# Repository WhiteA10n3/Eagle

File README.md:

# 开源硬件项目

设计软件使用Eagle

现包含：
### Unicon系列开发板

#### Un_51
#### Un_Arduino
#### Un_ARM7
#### Un_AVR
#### Un_Battery
#### Un_Bus
#### Un_C8051F
#### Un_GPS
#### Un_Moto
#### Un_Net
#### Un_RF
#### Un_SecUSB
#### Un_TTL
#### Un_Usb
#### Un_Zigbee

多年前画的板子，会陆续开源出来
供大家学习使用
祝玩的愉快

@WhiteA10n3
2018.9.13

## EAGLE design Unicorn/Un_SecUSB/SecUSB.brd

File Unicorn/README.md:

# Unicon系列开发板

设计软件使用Eagle

#### Un_51
#### Un_Arduino
#### Un_ARM7
#### Un_AVR
#### Un_Battery
#### Un_Bus
#### Un_C8051F
#### Un_GPS
#### Un_Moto
#### Un_Net
#### Un_RF
#### Un_SecUSB
#### Un_TTL
#### Un_Usb
#### Un_Zigbee

@WhiteA10n3

2018.9.13

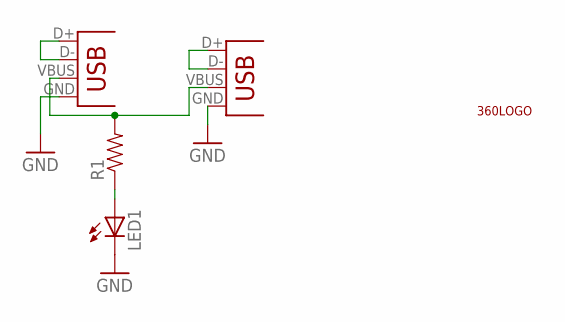
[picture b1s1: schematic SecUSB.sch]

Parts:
LED1: LED0603; LED-0603
R1: RESISTOR0603-RES; 0603-RES
U$1: 360LOGO_0.8
X2: USB_4-A-H_2; USB-A-H_2
X3: USB_4_3; USB-A-3

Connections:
GND: LED1.C, X2.GND, X3.GND
unnamed: R1.2, X2.VBUS, X3.VBUS
unnamed: X2.D+, X2.D-
unnamed: X3.D+, X3.D-
unnamed: LED1.A, R1.1

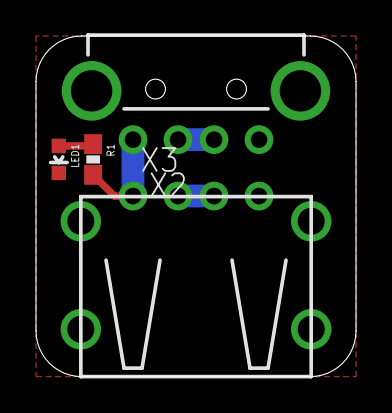
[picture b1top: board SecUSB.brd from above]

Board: 2 copper layers, 17.8 x 18.9 mm, 5 parts (1 on the bottom side), 5 nets.

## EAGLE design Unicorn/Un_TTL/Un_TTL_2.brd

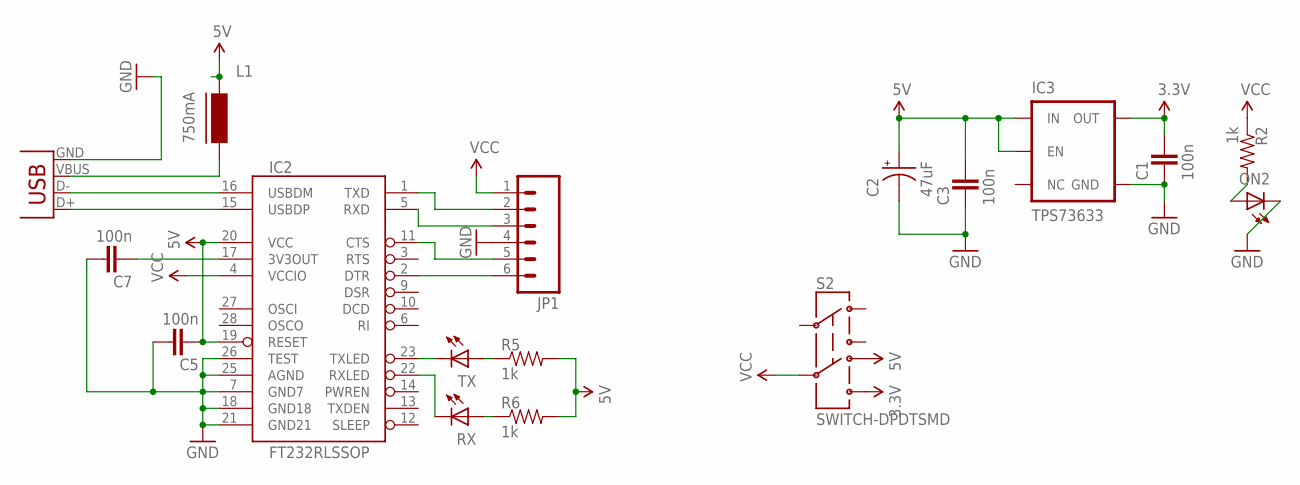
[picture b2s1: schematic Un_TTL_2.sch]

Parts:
C1, C3, C5, C7: 100n; 0603-CAP
C2: 47uF; EIA3216
IC2: FT232RLSSOP; SSOP28DB
IC3: TPS73633; SOT23-5
JP1: M06SIP; 1X06
L1: 750mA; FB805
ON2: LED0603; LED-0603
R2, R5, R6: 1k; 0603-RES
RX: LED0603; LED-0603
S2: SWITCH-DPDTSMD; AYZ0202
TX: LED0603; LED-0603
X2: USB_4-A-H; USB-A-H

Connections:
3.3V: C1.1, IC3.5 (OUT), S2.6
5V: C2.A (+), C3.1, C5.2, IC2.19 (RESET), IC2.20 (VCC), IC3.1 (IN), IC3.3 (EN), L1.1, R5.2, R6.2, S2.4
DTR: IC2.11 (CTS), JP1.5
GND: C1.2, C2.C (-), C3.2, C5.1, C7.1, IC2.7 (GND7), IC2.18 (GND18), IC2.21 (GND21), IC2.25 (AGND), IC2.26 (TEST), IC3.2 (GND), JP1.4, ON2.C, X2.GND
unnamed: L1.2, X2.VBUS
unnamed: ON2.A, R2.2
unnamed: R5.1, TX.A
unnamed: IC2.2 (DTR), JP1.6
unnamed: IC2.16 (USBDM), X2.D-
unnamed: IC2.15 (USBDP), X2.D+
unnamed: IC2.23 (TXLED), TX.C
unnamed: R6.1, RX.A
unnamed: IC2.22 (RXLED), RX.C
unnamed: C7.2, IC2.17 (3V3OUT)
RXD: IC2.5 (RXD), JP1.3
TXD: IC2.1 (TXD), JP1.2
VCC: IC2.4 (VCCIO), JP1.1, R2.1, S2.5

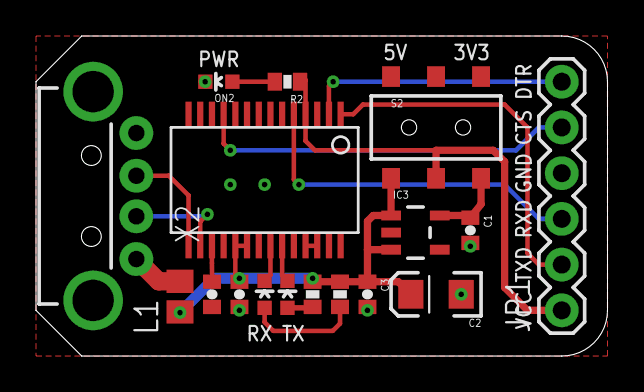
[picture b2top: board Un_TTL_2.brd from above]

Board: 2 copper layers, 31.8 x 17.8 mm, 17 parts (0 on the bottom side), 17 nets.

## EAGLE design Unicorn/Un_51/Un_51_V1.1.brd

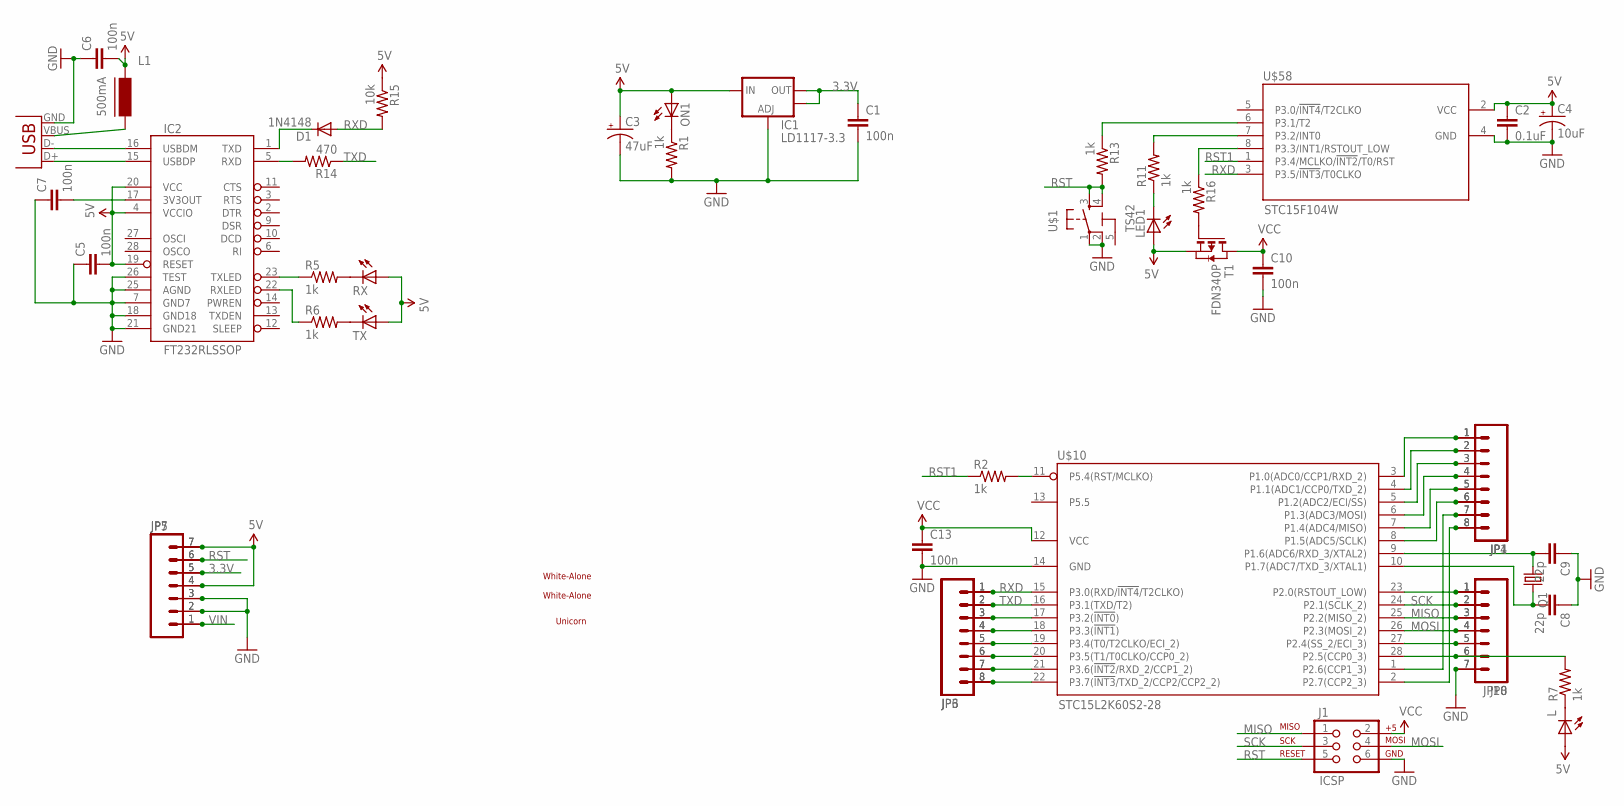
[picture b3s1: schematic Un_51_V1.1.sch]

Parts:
C1, C5, C6, C7, C10, C13: 100n; 0603-CAP
C2: 0.1uF; 0603-CAP
C3: 47uF; PANASONIC_D
C4: 10uF; EIA3216
C8, C9: 22p; 0603-CAP
D1: 1N4148; SOD-323
IC1: LD1117-3.3; SOT223
IC2: FT232RLSSOP; SSOP28DB
J1: ICSP; 2X3
JP1, JP4: M081X08; 1X08
JP3, JP6: M08; 1X08
JP5, JP7, JP8, JP10: M07; 1X07
L: LED0805; LED-0805
L1: 500mA; FB805
LED1: LED0805; LED-0805
ON1: LED0805; LED-0805
Q1: CRYSTALHC49US; HC49US
R1, R2, R5, R6, R7, R11, R13, R16: 1k; 0603-RES
R14: 470; 0603-RES
R15: 10k; 0603-RES
RX: LED0805; LED-0805
T1: FDN340P; SOT-23
TX: LED0805; LED-0805
U$1: TS42
U$3: UNICORN; UNICORN_1
U$7, U$11: WHITE-ALONE_0
U$10: STC15L2K60S2-28; SO-28W
U$58: STC15F104W; SO08
X1: USBSMD; USB-MINIB

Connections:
3.3V: C1.1, IC1.2 (OUT), IC1.4 (OUT), JP5.5, JP7.5
5V: C2.1, C3.+, C4.A (+), C5.2, C6.2, IC1.3 (IN), IC2.4 (VCCIO), IC2.19 (RESET), IC2.20 (VCC), JP5.4, JP5.7, JP7.4, JP7.7, L.1 (A), L1.1, LED1.1 (A), ON1.1 (A), R15.1, RX.1 (A), T1.2 (S), TX.1 (A), U$58.2 (VCC)
GND: C1.2, C2.2, C3.-, C4.C (-), C5.1, C6.1, C7.1, C8.1, C9.1, C10.2, C13.2, IC1.1 (ADJ), IC2.7 (GND7), IC2.18 (GND18), IC2.21 (GND21), IC2.25 (AGND), IC2.26 (TEST), J1.6, JP5.2, JP5.3, JP7.2, JP7.3, JP8.7, JP10.7, R1.2, U$1.1, U$1.2, U$10.14 (GND), U$58.4 (GND), X1.GND
MISO: J1.1, JP8.3, JP10.3, U$10.25 (P2.2(MISO_2))
MOSI: J1.4, JP8.4, JP10.4, U$10.26 (P2.3(MOSI_2))
unnamed: JP1.6, JP4.6, U$10.8 (P1.5(ADC5/SCLK))
unnamed: JP1.5, JP4.5, U$10.7 (P1.4(ADC4/MISO))
unnamed: L1.2, X1.VBUS
unnamed: LED1.2 (C), R11.1
unnamed: IC2.16 (USBDM), X1.D-
unnamed: IC2.15 (USBDP), X1.D+
unnamed: IC2.23 (TXLED), R5.1
unnamed: R5.2, RX.2 (C)
unnamed: R6.2, TX.2 (C)
unnamed: IC2.22 (RXLED), R6.1
unnamed: JP3.8, JP6.8, U$10.22 (P3.7(!INT3!/TXD_2/CCP2/CCP2_2))
unnamed: JP1.4, JP4.4, U$10.6 (P1.3(ADC3/MOSI))
unnamed: JP1.3, JP4.3, U$10.5 (P1.2(ADC2/ECI/SS))
unnamed: JP1.2, JP4.2, U$10.4 (P1.1(ADC1/CCP0/TXD_2))
unnamed: JP3.7, JP6.7, U$10.21 (P3.6(!INT2!/RXD_2/CCP1_2))
unnamed: JP8.1, JP10.1, U$10.23 (P2.0(RSTOUT_LOW))
unnamed: JP1.1, JP4.1, U$10.3 (P1.0(ADC0/CCP1/RXD_2))
unnamed: JP1.7, JP4.7, U$10.1 (P2.6(CCP1_3))
unnamed: JP1.8, JP4.8, U$10.2 (P2.7(CCP2_3))
unnamed: R11.2, U$58.7 (P3.2/INT0)
unnamed: L.2 (C), R7.1
unnamed: C7.2, IC2.17 (3V3OUT)
unnamed: R2.2, U$10.11 (P5.4(RST/MCLKO))
unnamed: JP3.3, JP6.3, U$10.17 (P3.2(!INT0!))
unnamed: JP3.4, JP6.4, U$10.18 (P3.3(!INT1!))
unnamed: JP3.5, JP6.5, U$10.19 (P3.4(T0/T2CLKO/ECI_2))
unnamed: JP3.6, JP6.6, U$10.20 (P3.5(T1/T0CLKO/CCP0_2))
unnamed: R16.1, U$58.8 (P3.3/INT1/RSTOUT_LOW)
unnamed: JP8.6, JP10.6, R7.2, U$10.28 (P2.5(CCP0_3))
unnamed: ON1.2 (C), R1.1
unnamed: R13.1, U$58.6 (P3.1/T2)
unnamed: IC2.5 (RXD), R14.2
unnamed: D1.1 (C), IC2.1 (TXD)
unnamed: C8.2, Q1.2, U$10.10 (P1.7(ADC7/TXD_3/XTAL1))
unnamed: C9.2, Q1.1, U$10.9 (P1.6(ADC6/RXD_3/XTAL2))
unnamed: R16.2, T1.3 (G)
unnamed: JP8.5, JP10.5, U$10.27 (P2.4(SS_2/ECI_3))
RST: J1.5, JP5.6, JP7.6, R13.2, U$1.3, U$1.4
RST1: R2.1, U$58.1 (P3.4/MCLKO/!INT2!/T0/RST)
RXD: D1.2 (A), JP3.1, JP6.1, R15.2, U$10.15 (P3.0(RXD/!INT4!/T2CLKO)), U$58.3 (P3.5/!INT3!/T0CLKO)
SCK: J1.3, JP8.2, JP10.2, U$10.24 (P2.1(SCLK_2))
TXD: JP3.2, JP6.2, R14.1, U$10.16 (P3.1(TXD/T2))
VCC: C10.1, C13.1, J1.2, T1.1 (D), U$10.12 (VCC)
VIN: JP5.1, JP7.1

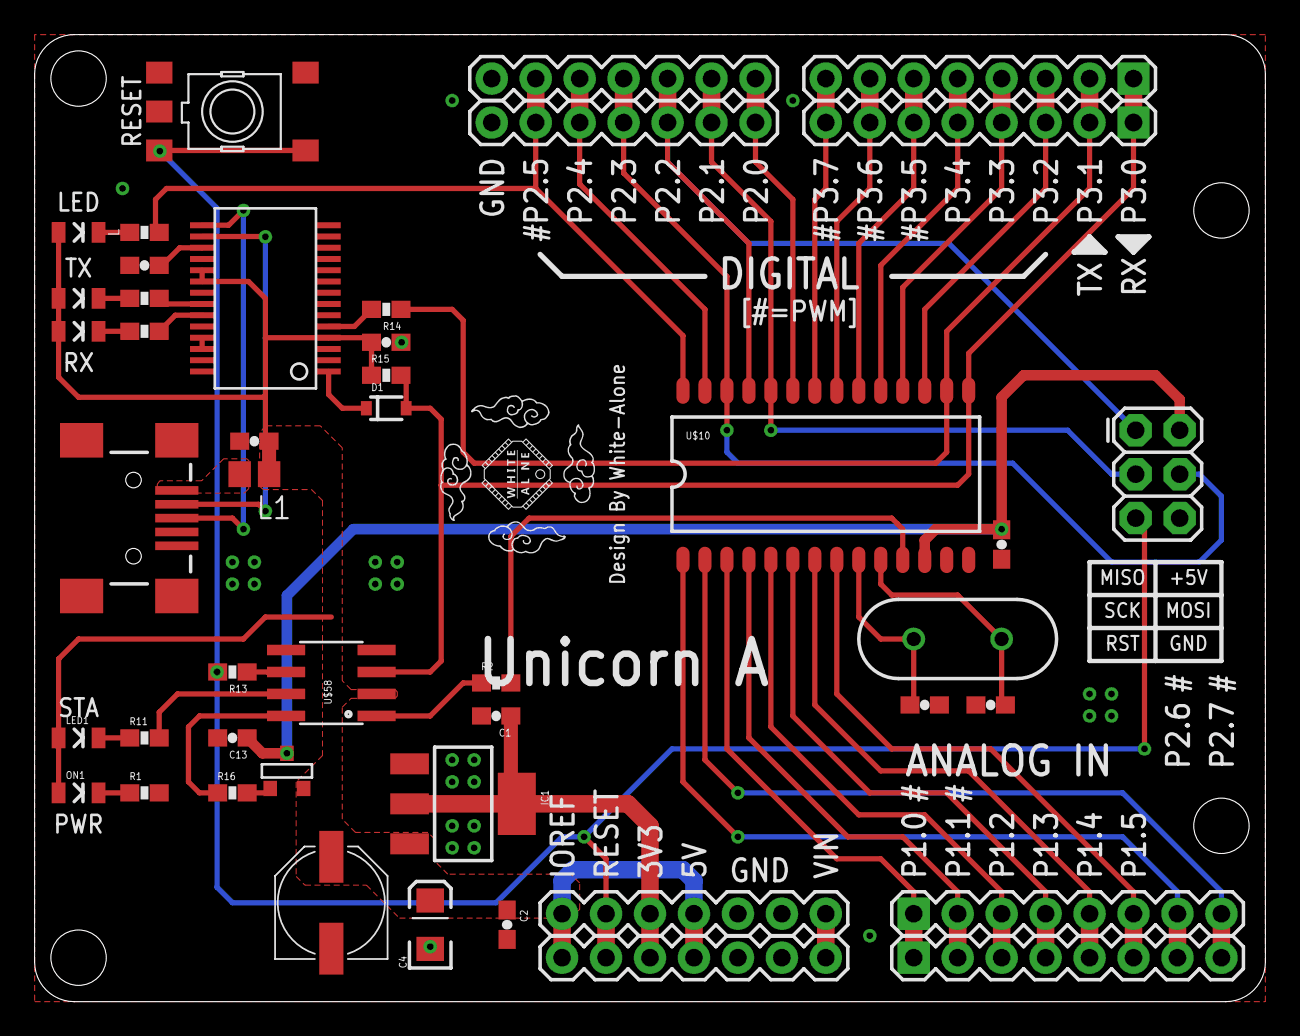
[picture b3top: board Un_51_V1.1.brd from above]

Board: 2 copper layers, 71.1 x 55.9 mm, 48 parts (1 on the bottom side), 49 nets.

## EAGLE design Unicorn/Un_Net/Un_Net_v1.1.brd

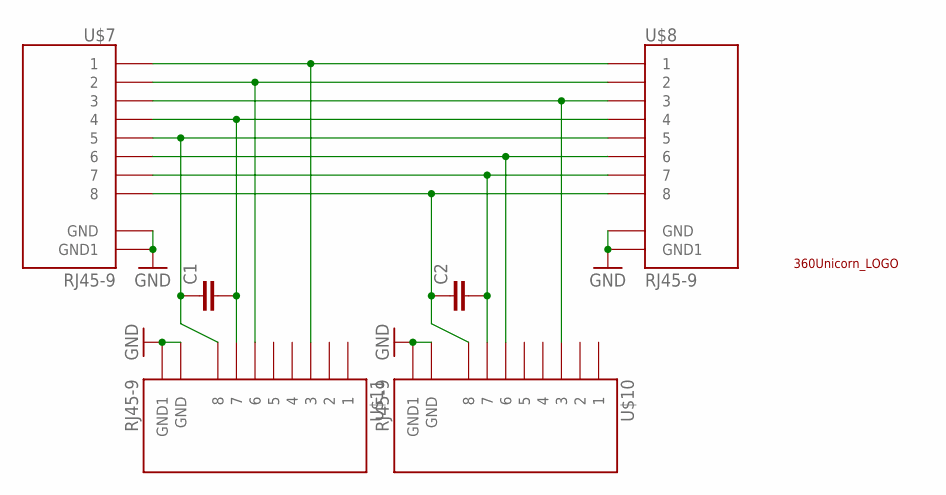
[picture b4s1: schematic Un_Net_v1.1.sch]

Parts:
C1, C2: CAP1206; 1206
U$1: 360UNICORN_LOGO_1Z
U$7, U$8, U$10, U$11: RJ45-9

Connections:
GND: U$7.9 (GND), U$7.10 (GND1), U$8.9 (GND), U$8.10 (GND1), U$10.9 (GND), U$10.10 (GND1), U$11.9 (GND), U$11.10 (GND1)
unnamed: U$7.1, U$8.1, U$11.3
unnamed: U$7.2, U$8.2, U$11.6
unnamed: U$7.3, U$8.3, U$10.3
unnamed: C2.2, U$7.7, U$8.7, U$10.7
unnamed: U$7.6, U$8.6, U$10.6
unnamed: C1.1, U$7.5, U$8.5, U$11.8
unnamed: C1.2, U$7.4, U$8.4, U$11.7
unnamed: C2.1, U$7.8, U$8.8, U$10.8

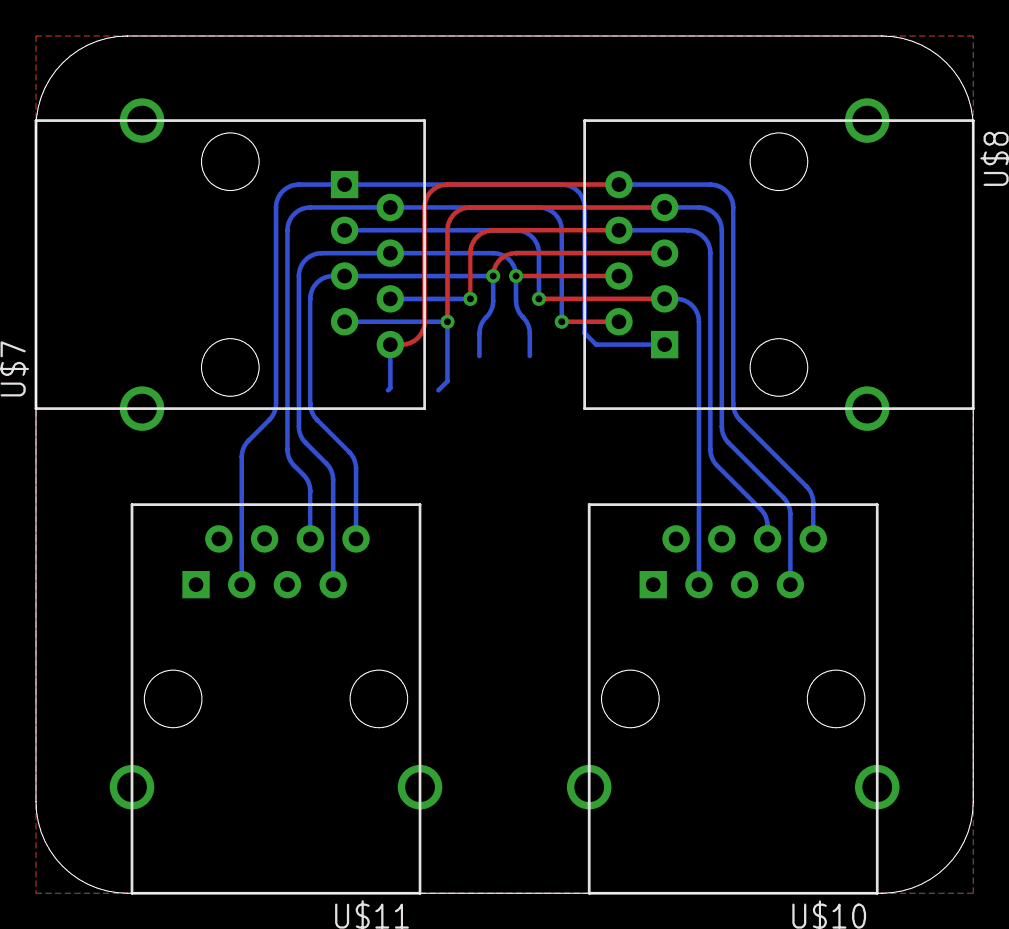
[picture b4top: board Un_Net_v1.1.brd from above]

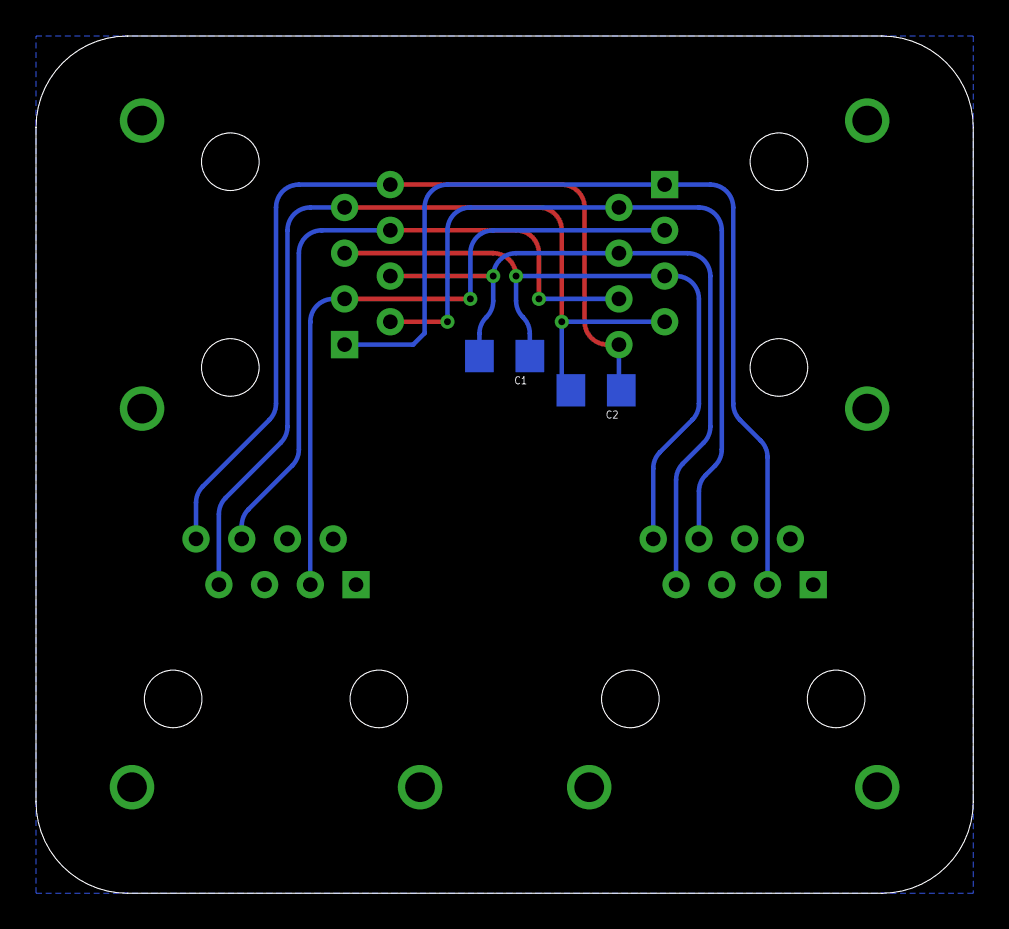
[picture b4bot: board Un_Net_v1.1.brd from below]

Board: 2 copper layers, 52.1 x 47.6 mm, 7 parts (3 on the bottom side), 9 nets.

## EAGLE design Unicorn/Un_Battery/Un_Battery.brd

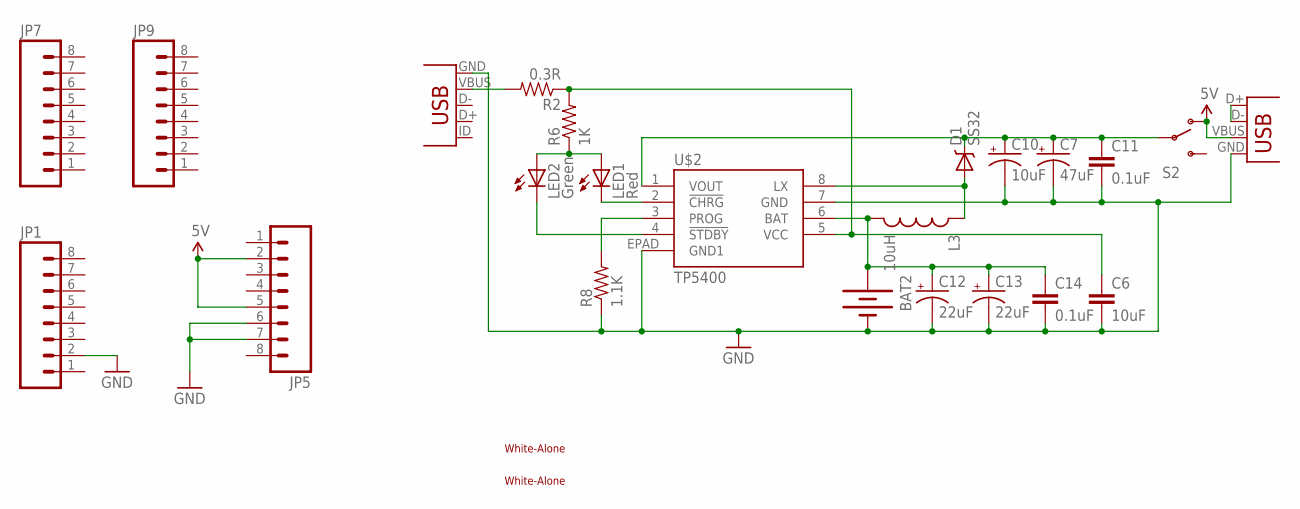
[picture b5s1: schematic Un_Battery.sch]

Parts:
BAT2: BATTERYLIPO; BATTERY-LIPO
C6: 10uF; 1206
C7: 47uF; PANASONIC_D
C10: 10uF; EIA3216
C11, C14: 0.1uF; 1206
C12, C13: 22uF; EIA3216
D1: SS32; SMA-DIODE
JP1, JP5, JP7, JP9: M081X08; 1X08
L3: 10uH; CR75
LED1: Red; LED-0805
LED2: Green; LED-0805
R2: 0.3R; 1206
R6: 1K; 0805
R8: 1.1K; 0805
S2: SWITCH-SPST; SWITCH-SPDT2
U$2: TP5400; SO08-EPAD
U$4, U$5: WHITE-ALONE_2
U$6: USB_5-SMD; USB-MINIB
X2: USB-A-S

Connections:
5V: JP5.2, JP5.5, S2.1 (O), X2.VBUS
GND: BAT2.-, C6.2, C7.-, C10.C (-), C11.2, C12.C (-), C13.C (-), C14.2, JP1.2, JP5.6, JP5.7, R8.1, U$2.7 (GND), U$2.EPAD (GND1), U$6.GND, X2.GND
unnamed: R2.2, U$6.VBUS
unnamed: C6.1, R2.1, R6.2, U$2.5 (VCC)
unnamed: LED1.1 (A), LED2.1 (A), R6.1
unnamed: LED2.2 (C), U$2.4 (!STDBY)
unnamed: LED1.2 (C), U$2.2 (!CHRG)
unnamed: C7.+, C10.A (+), C11.1, D1.C, S2.2, U$2.1 (VOUT)
unnamed: R8.2, U$2.3 (PROG)
unnamed: D1.A, L3.P$1 (1), U$2.8 (LX)
unnamed: X2.D+, X2.D-
unnamed: BAT2.+, C12.A (+), C13.A (+), C14.1, L3.P$2 (2), U$2.6 (BAT)

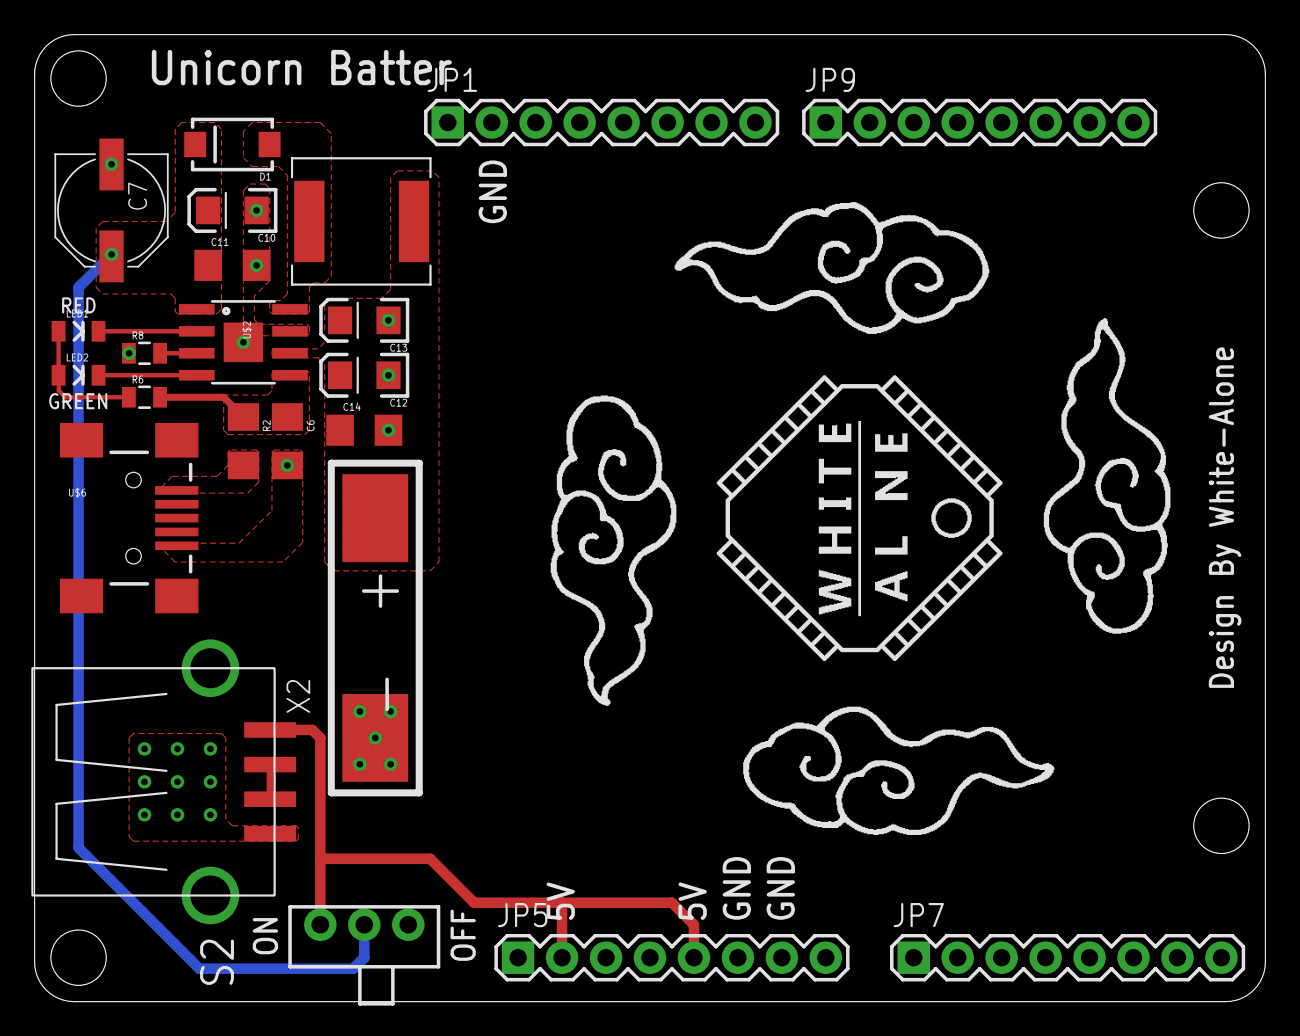
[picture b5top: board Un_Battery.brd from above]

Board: 2 copper layers, 71.1 x 55.9 mm, 25 parts (1 on the bottom side), 12 nets.

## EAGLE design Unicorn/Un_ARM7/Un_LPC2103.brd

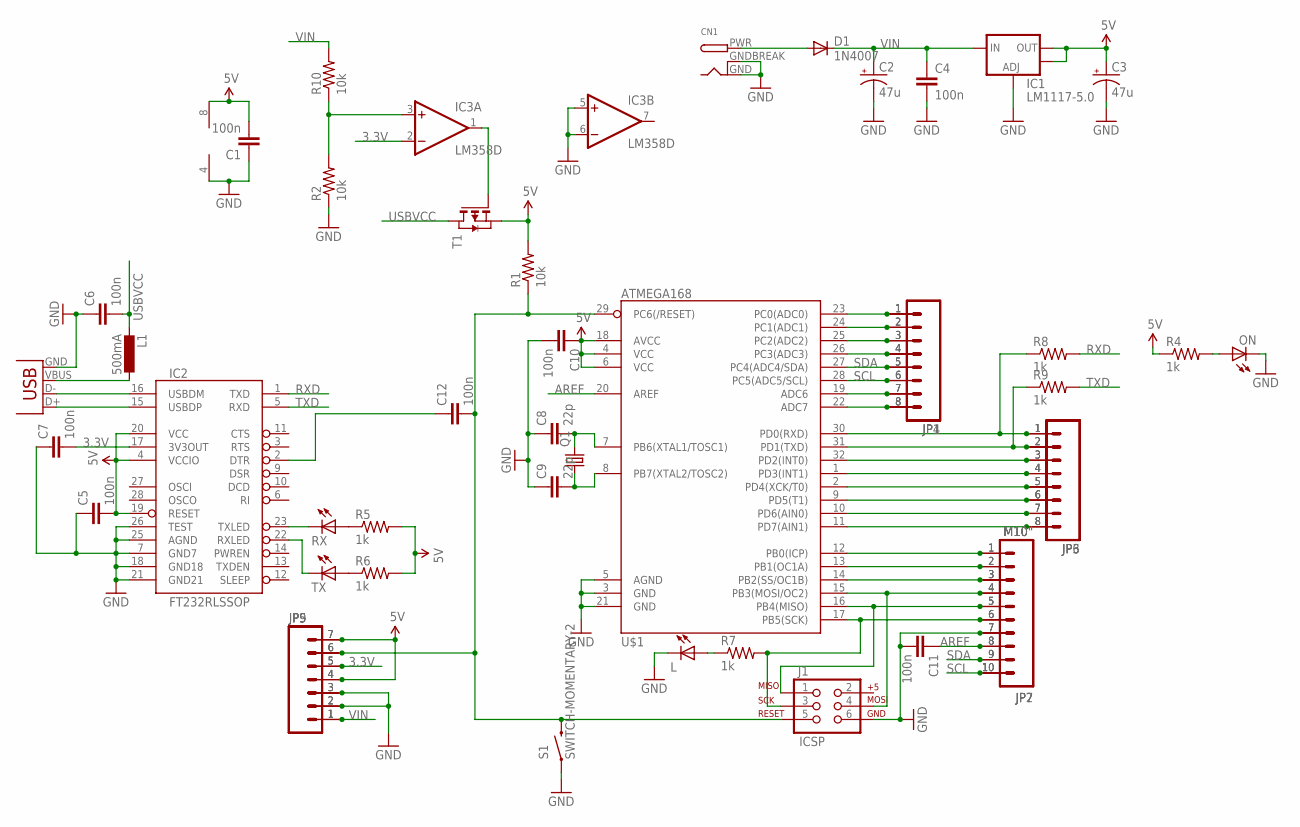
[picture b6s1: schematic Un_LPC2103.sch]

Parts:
C1, C4, C5, C6, C7, C10, C11, C12: 100n; 0603-CAP
C2, C3: 47u; PANASONIC_D
C8, C9: 22p; 0805
CN1: DCBARRELPTH; DCJACK_2MM_PTH
D1: 1N4007; SMB
IC1: LM1117-5.0; SOT223
IC2: FT232RLSSOP; SSOP28DB
IC3: LM358D; SO08
J1: ICSP; 2X3
JP1, JP4: M081X08; 1X08
JP2, JP7: M10"; 1X10
JP3, JP6: M08; 1X08
JP5, JP9: M07; 1X07
L: LED0805; LED-0805
L1: 500mA; L1812
ON: LED0805; LED-0805
Q1: CRYSTALHC49US; HC49US
R1, R2, R10: 10k; 0805
R4, R5, R6, R7, R8, R9: 1k; 0805
RX: LED0805; LED-0805
S1: SWITCH-MOMENTARY-2; TACTILE_SWITCH_TALL
T1: PMOSSOT23; SOT-23
TX: LED0805; LED-0805
U$1: ATMEGA168; TQFP32-08
X1: USBPTH; USB-B-PTH

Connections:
3.3V: C7.2, IC2.17 (3V3OUT), IC3.2 (-IN), JP5.5, JP9.5
5V: C1.2, C3.+, C5.2, C10.1, IC1.2 (OUT), IC1.4 (OUT), IC2.4 (VCCIO), IC2.19 (RESET), IC2.20 (VCC), IC3.8 (V+), JP5.4, JP5.7, JP9.4, JP9.7, R1.2, R4.1, R5.2, R6.2, T1.2 (S), U$1.4 (VCC), U$1.6 (VCC), U$1.18 (AVCC)
A0: JP1.1, JP4.1, U$1.23 (PC0(ADC0))
AREF: C11.1, JP2.8, JP7.8, U$1.20 (AREF)
GND: C1.1, C2.-, C3.-, C4.2, C5.1, C6.1, C7.1, C8.1, C9.1, C10.2, C11.2, CN1.GND, CN1.GNDBREAK, IC1.1 (ADJ), IC2.7 (GND7), IC2.18 (GND18), IC2.21 (GND21), IC2.25 (AGND), IC2.26 (TEST), IC3.4 (V-), IC3.5 (+IN), IC3.6 (-IN), J1.6, JP2.7, JP5.2, JP5.3, JP7.7, JP9.2, JP9.3, L.2 (C), ON.2 (C), R2.1, S1.A2 (1), U$1.3 (GND), U$1.5 (AGND), U$1.21 (GND), X1.GND
IO0: JP3.1, JP6.1, R8.1, U$1.30 (PD0(RXD))
unnamed: IC3.3 (+IN), R2.2, R10.1
unnamed: IC3.1 (OUT), T1.3 (G)
unnamed: L1.1, X1.VBUS
unnamed: CN1.PWR, D1.A
unnamed: IC2.16 (USBDM), X1.D-
unnamed: IC2.15 (USBDP), X1.D+
unnamed: R5.1, RX.1 (A)
unnamed: R6.1, TX.1 (A)
unnamed: IC2.23 (TXLED), RX.2 (C)
unnamed: IC2.22 (RXLED), TX.2 (C)
unnamed: JP1.7, JP4.7, U$1.19 (ADC6)
unnamed: JP1.8, JP4.8, U$1.22 (ADC7)
unnamed: L.1 (A), R7.1
unnamed: C12.1, IC2.2 (DTR)
unnamed: JP2.1, JP7.1, U$1.12 (PB0(ICP))
unnamed: JP2.2, JP7.2, U$1.13 (PB1(OC1A))
unnamed: JP2.3, JP7.3, U$1.14 (PB2(SS/OC1B))
unnamed: J1.4, JP2.4, JP7.4, U$1.15 (PB3(MOSI/OC2))
unnamed: J1.1, JP2.5, JP7.5, U$1.16 (PB4(MISO))
unnamed: JP3.2, JP6.2, R9.1, U$1.31 (PD1(TXD))
unnamed: JP3.3, JP6.3, U$1.32 (PD2(INT0))
unnamed: JP3.4, JP6.4, U$1.1 (PD3(INT1))
unnamed: JP3.5, JP6.5, U$1.2 (PD4(XCK/T0))
unnamed: JP3.6, JP6.6, U$1.9 (PD5(T1))
unnamed: JP3.7, JP6.7, U$1.10 (PD6(AIN0))
unnamed: JP3.8, JP6.8, U$1.11 (PD7(AIN1))
unnamed: JP1.2, JP4.2, U$1.24 (PC1(ADC1))
unnamed: JP1.3, JP4.3, U$1.25 (PC2(ADC2))
unnamed: JP1.4, JP4.4, U$1.26 (PC3(ADC3))
unnamed: ON.1 (A), R4.2
unnamed: C12.2, JP5.6, JP9.6, R1.1, S1.B2 (2), U$1.29 (PC6(/RESET))
unnamed: C8.2, Q1.2, U$1.7 (PB6(XTAL1/TOSC1))
unnamed: C9.2, Q1.1, U$1.8 (PB7(XTAL2/TOSC2))
RXD: IC2.1 (TXD), R8.2
SCK: JP2.6, JP7.6, R7.2, U$1.17 (PB5(SCK))
SCL: JP1.6, JP2.10, JP4.6, JP7.10, U$1.28 (PC5(ADC5/SCL))
SDA: JP1.5, JP2.9, JP4.5, JP7.9, U$1.27 (PC4(ADC4/SDA))
TXD: IC2.5 (RXD), R9.2
USBVCC: C6.2, L1.2, T1.1 (D)
VIN: C2.+, C4.1, D1.C, IC1.3 (IN), JP5.1, JP9.1, R10.2

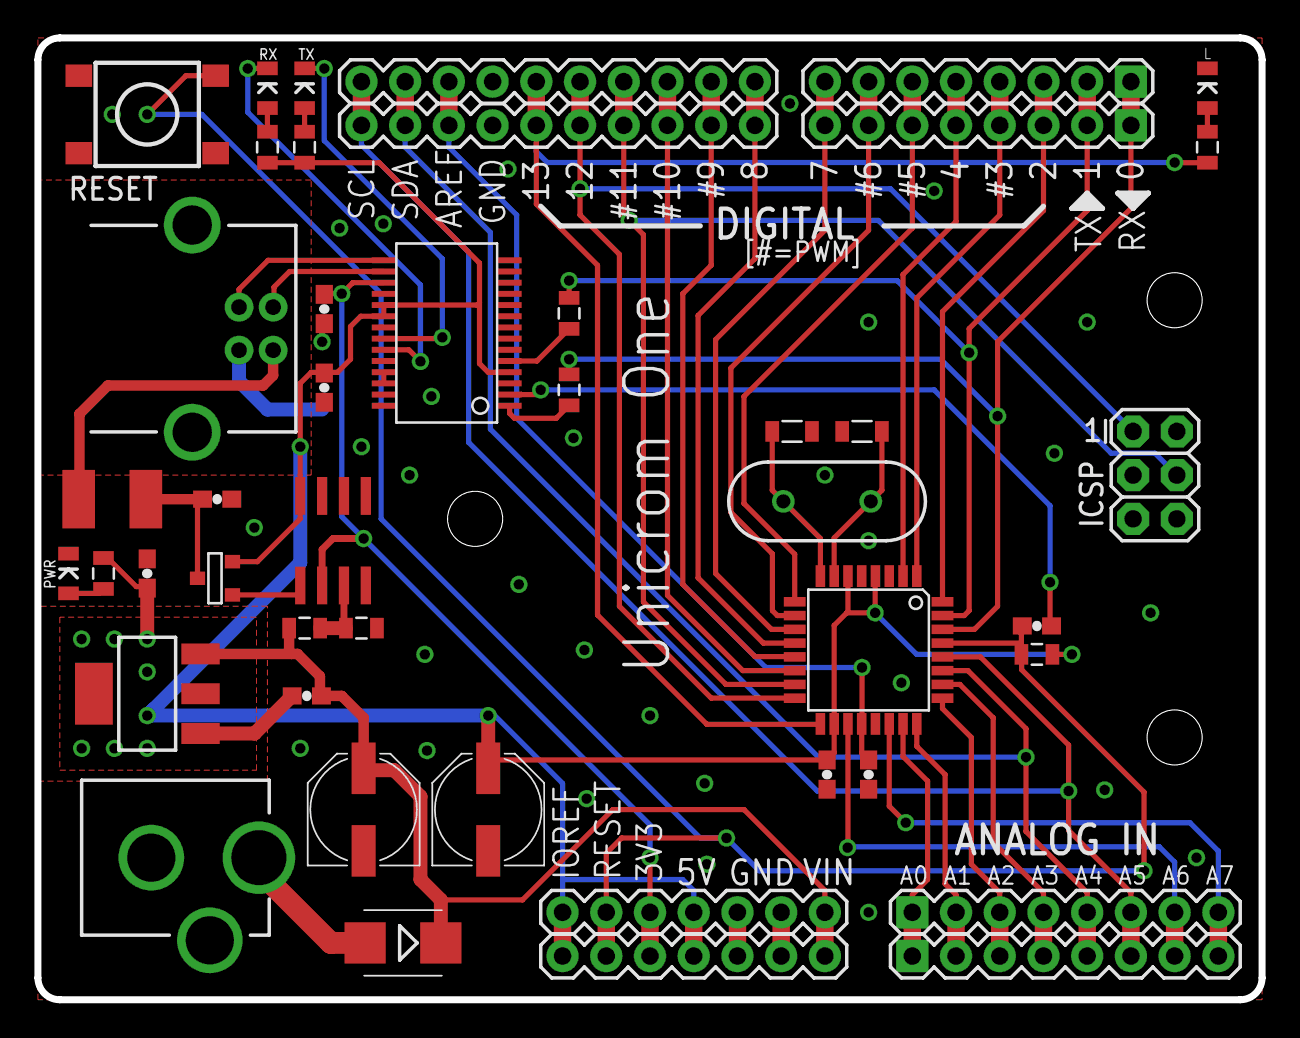
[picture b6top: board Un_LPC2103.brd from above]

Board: 2 copper layers, 71.1 x 55.9 mm, 45 parts (0 on the bottom side), 46 nets.

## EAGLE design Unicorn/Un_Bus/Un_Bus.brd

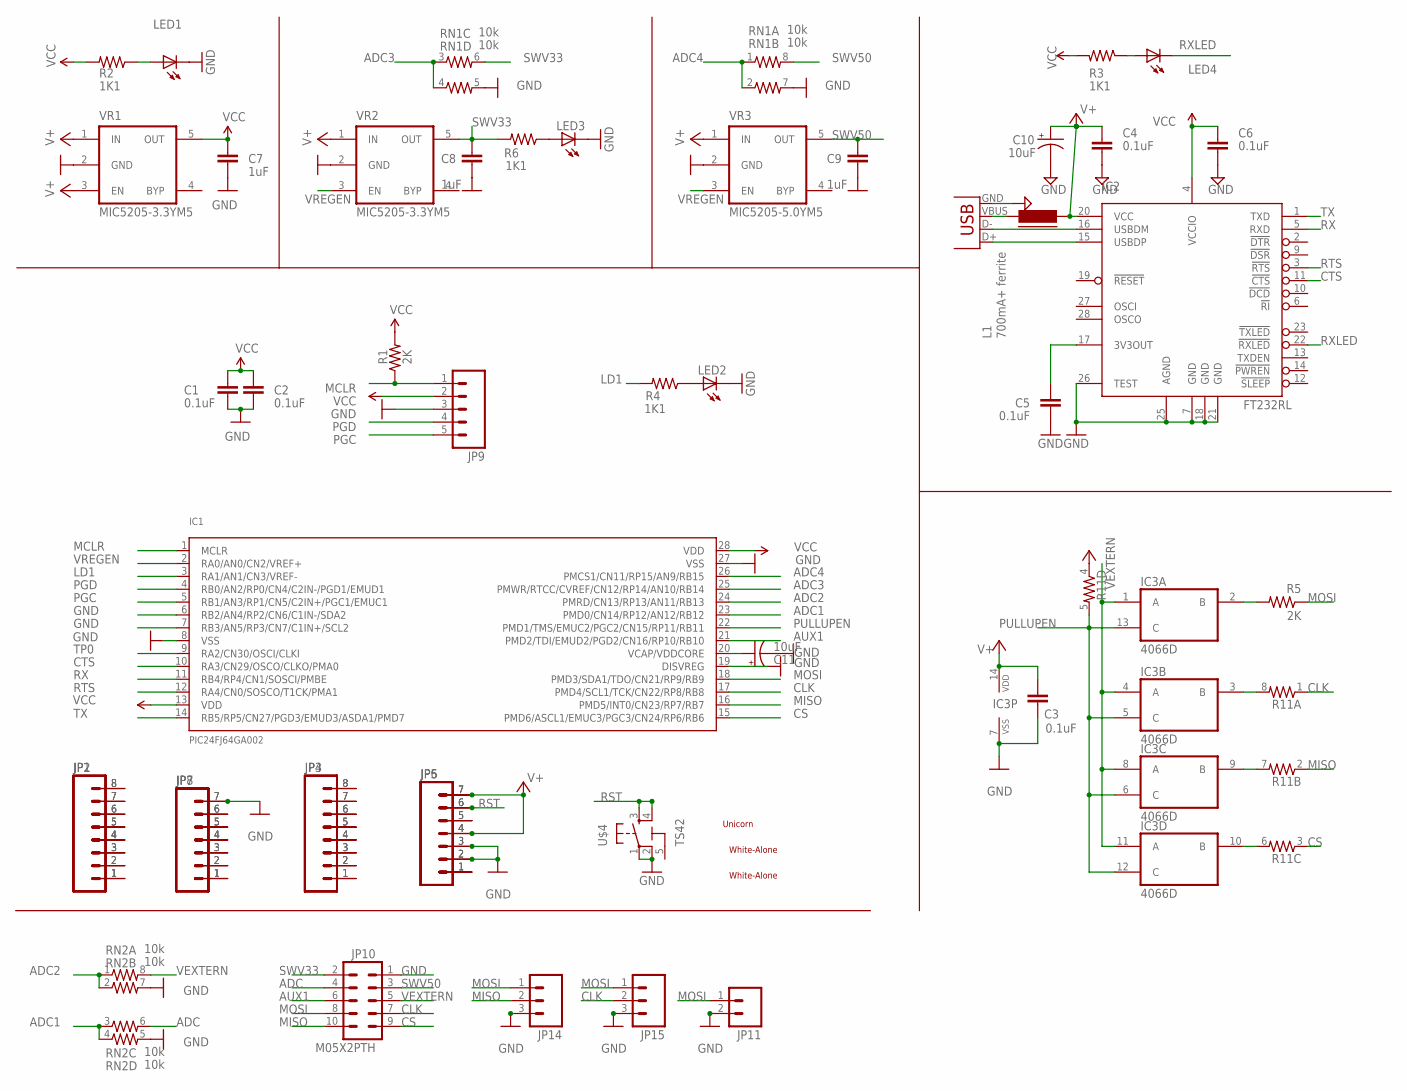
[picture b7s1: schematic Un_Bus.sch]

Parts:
C1, C2, C3, C4, C5, C6: 0.1uF; 0603-CAP
C7, C8, C9: 1uF; 0603-CAP
C10, C11: 10uF; EIA3216
IC1: PIC24FJ64GA002; SSOP28
IC2: FT232RL; SSOP28
IC3: 4066D; SO14
JP1, JP2, JP3, JP4: M081X08; 1X08
JP5, JP6, JP7, JP8: M07; 1X07
JP9: M05PTH; 1X05
JP10: M05X2PTH; AVR_ICSP
JP11: M02PTH; 1X02
JP14, JP15: M03PTH; 1X03
L1: 700mA+ ferrite; FB805
LED1, LED2, LED3, LED4: LED0805; LED-0805
R1, R5: 2K; 0603-RES
R2, R3, R4, R6: 1K1; 0603-RES
R11: RESISTOR-ARRAY; RES-NET-0603
RN1, RN2: 10k; RES-NET-0603
U$1: UNICORN; UNICORN_1
U$2, U$3: WHITE-ALONE_0
U$4: TS42
VR1, VR2: MIC5205-3.3YM5; SOT-23-5
VR3: MIC5205-5.0YM5; SOT-23-5
X1: USBSMD; USB-MINIB

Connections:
ADC: JP10.4, RN2.6 (2)
ADC1: IC1.23 (PMD0/CN14/RP12/AN12/RB12), RN2.3 (1), RN2.4 (1)
ADC2: IC1.24 (PMRD/CN13/RP13/AN11/RB13), RN2.1, RN2.2 (1)
ADC3: IC1.25 (PMWR/RTCC/CVREF/CN12/RP14/AN10/RB14), RN1.3 (1), RN1.4 (1)
ADC4: IC1.26 (PMCS1/CN11/RP15/AN9/RB15), RN1.1, RN1.2 (1)
AUX1: IC1.21 (PMD2/TDI/EMUD2/PGD2/CN16/RP10/RB10), JP10.6
CLK: IC1.17 (PMD4/SCL1/TCK/CN22/RP8/RB8), JP10.7, JP15.2, R11.1
CS: IC1.15 (PMD6/ASCL1/EMUC3/PGC3/CN24/RP6/RB6), JP10.9, R11.3 (1)
CTS: IC1.10 (RA3/CN29/OSCO/CLKO/PMA0), IC2.11 (!CTS)
GND: C1.2, C2.2, C3.2, C4.2, C5.2, C6.2, C7.2, C8.2, C9.2, C10.C (-), C11.C (-), IC1.6 (RB2/AN4/RP2/CN6/C1IN-/SDA2), IC1.7 (RB3/AN5/RP3/CN7/C1IN+/SCL2), IC1.8 (VSS), IC1.19 (DISVREG), IC1.27 (VSS), IC2.7 (GND), IC2.18 (GND), IC2.21 (GND), IC2.25 (AGND), IC2.26 (TEST), IC3.7 (VSS), JP5.2, JP5.3, JP6.2, JP6.3, JP7.7, JP8.7, JP9.3, JP10.1, JP11.2, JP14.3, JP15.3, LED1.2 (C), LED2.2 (C), LED3.2 (C), RN1.5 (2), RN1.7 (2), RN2.5 (2), RN2.7 (2), U$4.1, U$4.2, VR1.2 (GND), VR2.2 (GND), VR3.2 (GND), X1.GND
LD1: IC1.3 (RA1/AN1/CN3/VREF-), R4.2
MCLR: IC1.1 (MCLR), JP9.1, R1.1
MISO: IC1.16 (PMD5/INT0/CN23/RP7/RB7), JP10.10, JP14.2, R11.2 (1)
MOSI: IC1.18 (PMD3/SDA1/TDO/CN21/RP9/RB9), JP10.8, JP11.1, JP14.1, JP15.1, R5.1
unnamed: IC3.2 (B), R5.2
unnamed: IC3.3 (B), R11.8 (2)
unnamed: C11.A (+), IC1.20 (VCAP/VDDCORE)
unnamed: IC3.10 (B), R11.6 (2)
unnamed: IC3.9 (B), R11.7 (2)
unnamed: LED2.1 (A), R4.1
unnamed: LED1.1 (A), R2.1
unnamed: JP1.1, JP2.1
unnamed: C5.1, IC2.17 (3V3OUT)
unnamed: JP1.2, JP2.2
unnamed: JP1.3, JP2.3
unnamed: JP1.4, JP2.4
unnamed: LED4.1 (A), R3.1
unnamed: JP1.5, JP2.5
unnamed: IC2.15 (USBDP), X1.D+
unnamed: IC2.16 (USBDM), X1.D-
unnamed: JP1.6, JP2.6
unnamed: LED3.1 (A), R6.1
unnamed: JP1.7, JP2.7
unnamed: JP1.8, JP2.8
unnamed: JP3.1, JP4.1
unnamed: JP3.2, JP4.2
unnamed: JP3.3, JP4.3
unnamed: JP3.4, JP4.4
unnamed: JP3.5, JP4.5
unnamed: JP3.6, JP4.6
unnamed: JP3.7, JP4.7
unnamed: JP3.8, JP4.8
unnamed: JP5.1, JP6.1
unnamed: L1.1, X1.VBUS
unnamed: JP5.5, JP6.5
unnamed: JP7.1, JP8.1
unnamed: JP7.2, JP8.2
unnamed: JP7.3, JP8.3
unnamed: JP7.4, JP8.4
unnamed: JP7.5, JP8.5
unnamed: JP7.6, JP8.6
PGC: IC1.5 (RB1/AN3/RP1/CN5/C2IN+/PGC1/EMUC1), JP9.5
PGD: IC1.4 (RB0/AN2/RP0/CN4/C2IN-/PGD1/EMUD1), JP9.4
PULLUPEN: IC1.22 (PMD1/TMS/EMUC2/PGC2/CN15/RP11/RB11), IC3.5 (C), IC3.6 (C), IC3.12 (C), IC3.13 (C), R11.5 (2)
RST: JP5.6, JP6.6, U$4.3, U$4.4
RTS: IC1.12 (RA4/CN0/SOSCO/T1CK/PMA1), IC2.3 (!RTS)
RX: IC1.11 (RB4/RP4/CN1/SOSCI/PMBE), IC2.5 (RXD)
RXLED: IC2.22 (!RXLED), LED4.2 (C)
SWV33: C8.1, JP10.2, R6.2, RN1.6 (2), VR2.5 (OUT)
SWV50: C9.1, JP10.3, RN1.8 (2), VR3.5 (OUT)
TP0: IC1.9 (RA2/CN30/OSCI/CLKI)
TX: IC1.14 (RB5/RP5/CN27/PGD3/EMUD3/ASDA1/PMD7), IC2.1 (TXD)
V+: C3.1, C4.1, C10.A (+), IC2.20 (VCC), IC3.14 (VDD), JP5.4, JP5.7, JP6.4, JP6.7, L1.2, R11.4 (1), VR1.1 (IN), VR1.3 (EN), VR2.1 (IN), VR3.1 (IN)
VCC: C1.1, C2.1, C6.1, C7.1, IC1.13 (VDD), IC1.28 (VDD), IC2.4 (VCCIO), JP9.2, R1.2, R2.2, R3.2, VR1.5 (OUT)
VEXTERN: IC3.1 (A), IC3.4 (A), IC3.8 (A), IC3.11 (A), JP10.5, RN2.8 (2)
VREGEN: IC1.2 (RA0/AN0/CN2/VREF+), VR2.3 (EN), VR3.3 (EN)

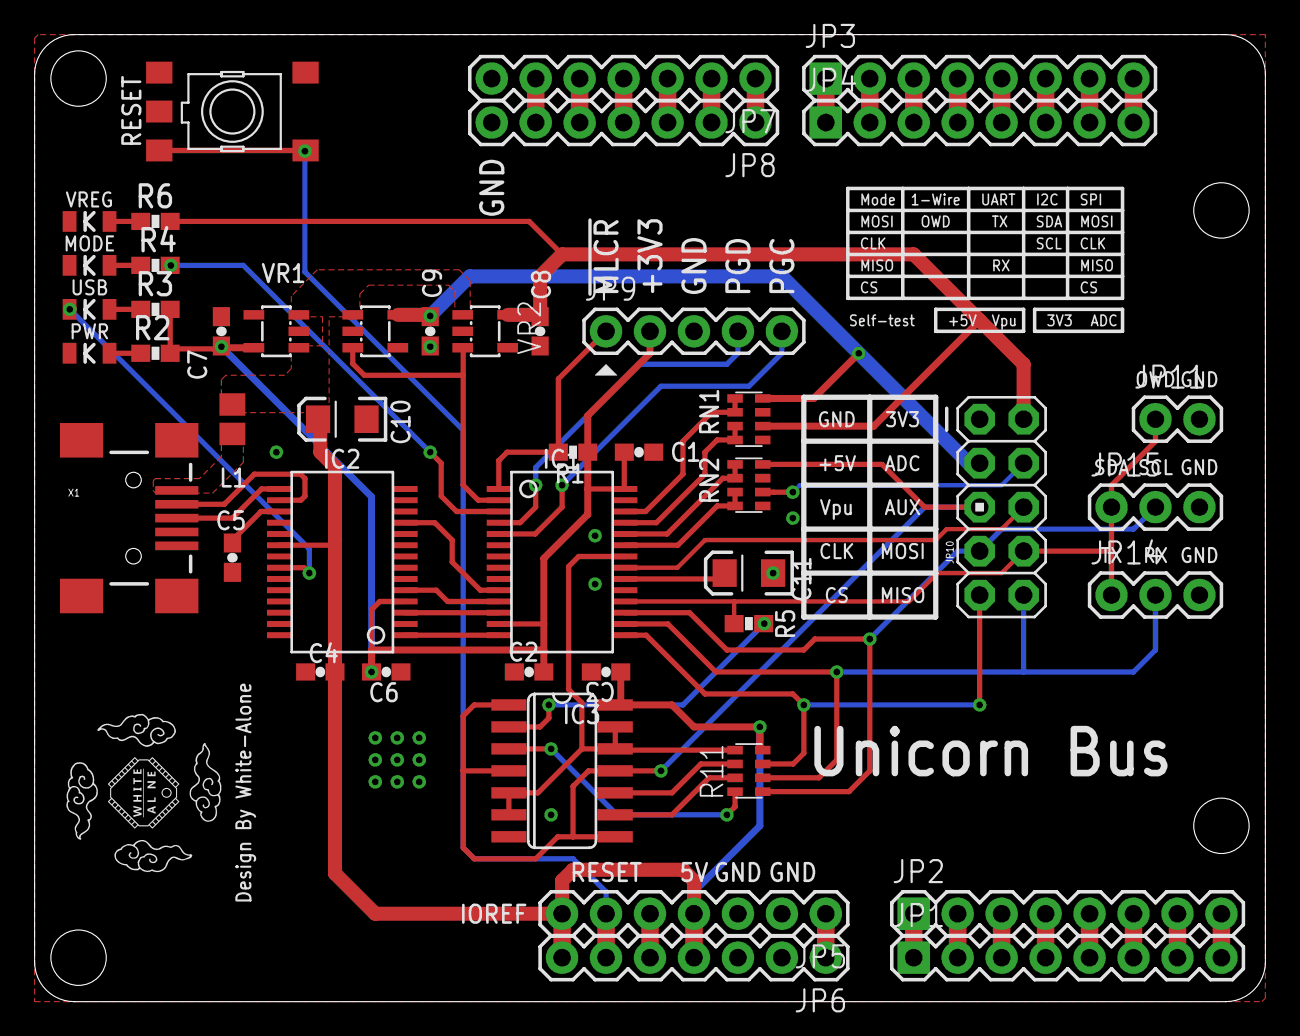
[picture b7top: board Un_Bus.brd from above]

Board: 2 copper layers, 71.1 x 55.9 mm, 49 parts (1 on the bottom side), 65 nets.

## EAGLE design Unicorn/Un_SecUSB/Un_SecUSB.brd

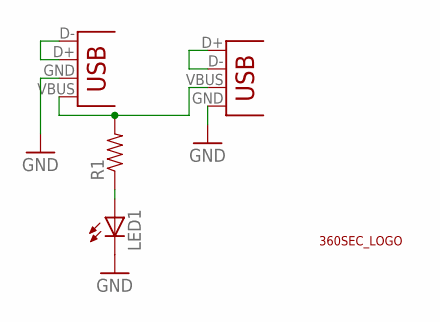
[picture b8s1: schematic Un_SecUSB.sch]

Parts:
LED1: LED0603; LED-0603
R1: RESISTOR0603-RES; 0603-RES
U$3: 360SEC_LOGO_0.8; 360SEC_0.8
X1: USB_4-A-H; USB-A-H
X2: USB_4_1; USB-A-1

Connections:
GND: LED1.C, X1.GND (VBUS), X2.GND
unnamed: R1.2, X1.VBUS (GND), X2.VBUS
unnamed: X1.D+ (D-), X1.D- (D+)
unnamed: X2.D+, X2.D-
unnamed: LED1.A, R1.1

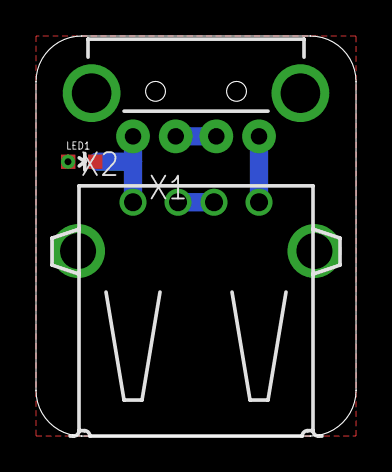
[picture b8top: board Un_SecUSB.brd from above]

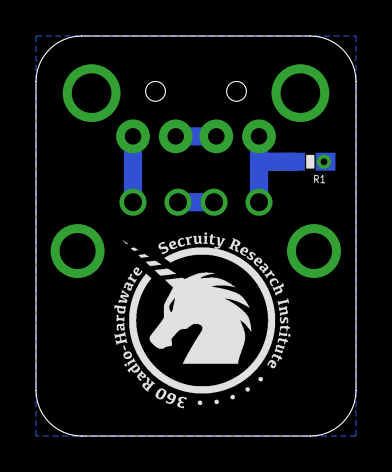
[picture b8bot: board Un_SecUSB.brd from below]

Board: 2 copper layers, 17.8 x 22.2 mm, 5 parts (2 on the bottom side), 5 nets.

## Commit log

2018-09-13 commit all file
2018-09-13 README

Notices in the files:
parts and their libraries:
1SparkFun: Licensing: CC v3.0 Share-Alike You are welcome to use this library for commercial purposes.
